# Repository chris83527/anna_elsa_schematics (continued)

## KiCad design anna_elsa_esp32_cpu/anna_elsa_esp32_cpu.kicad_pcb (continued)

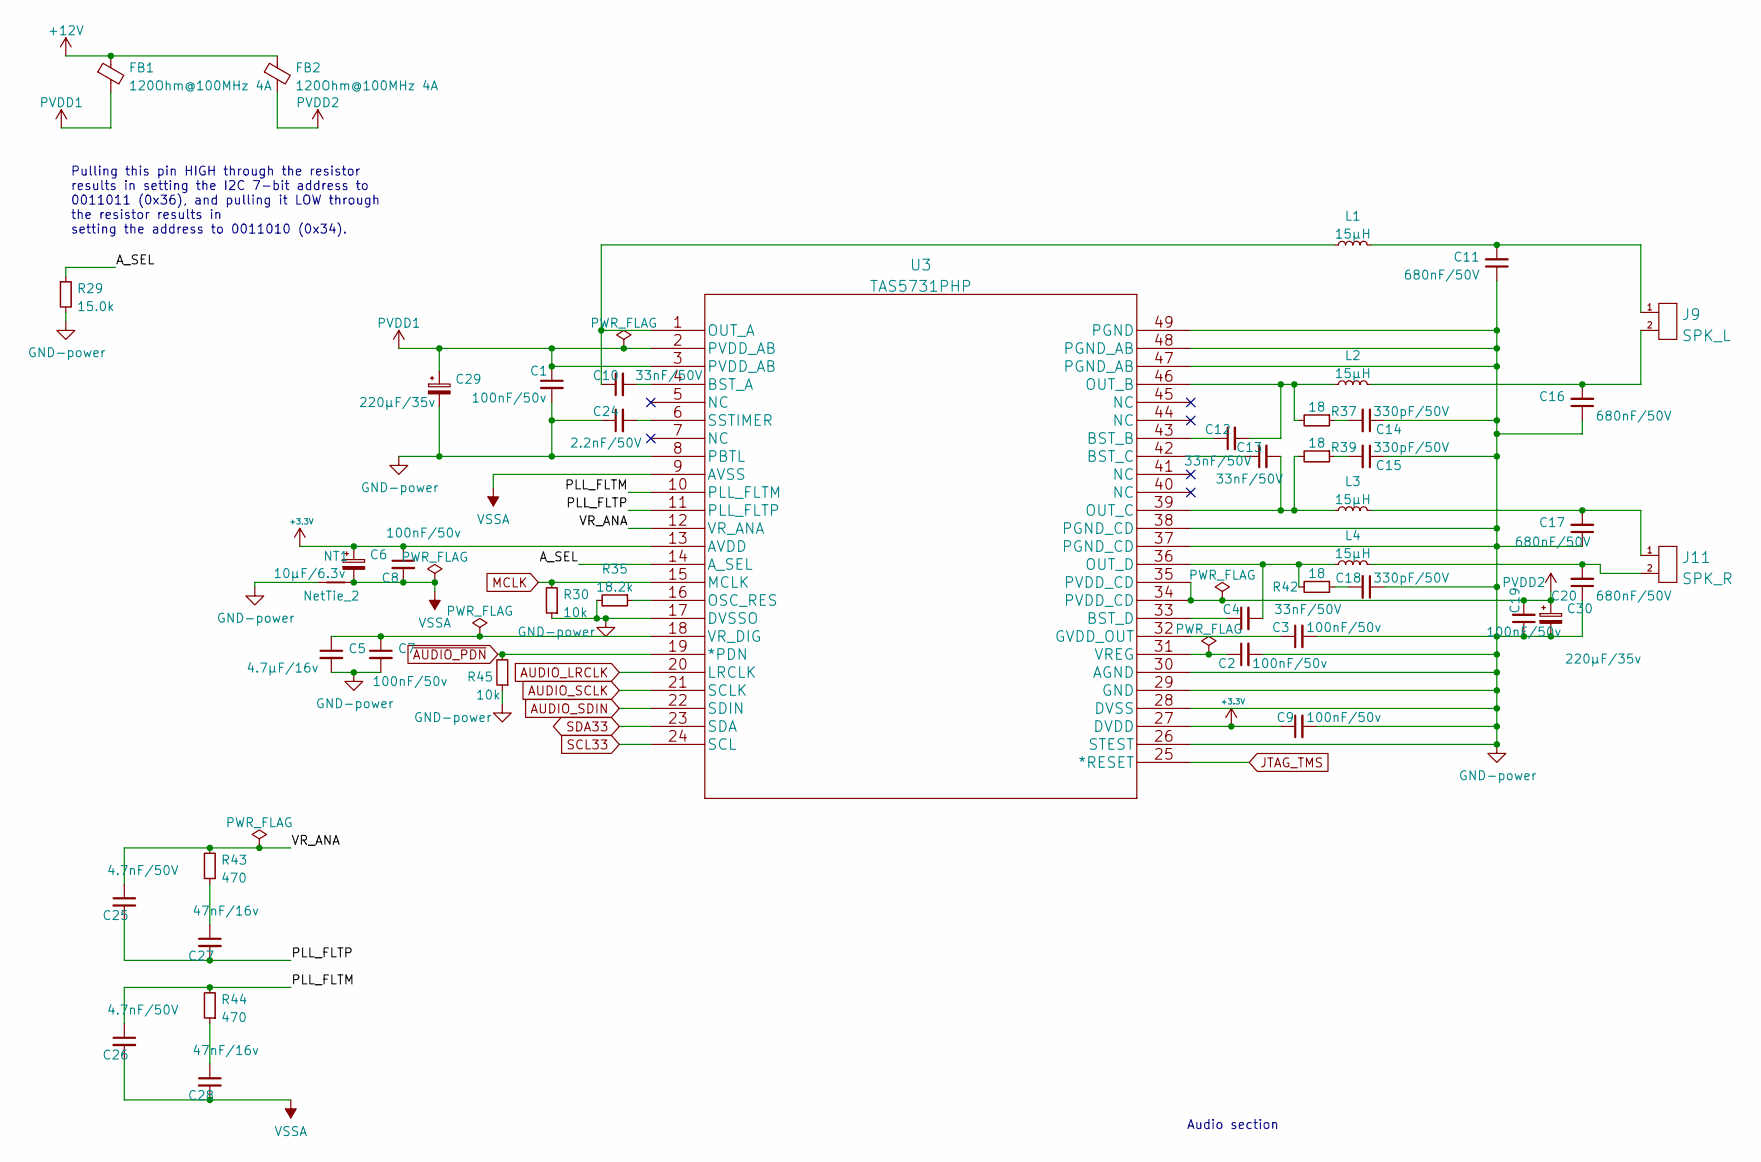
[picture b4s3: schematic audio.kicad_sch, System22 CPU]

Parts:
C1: 100nF/50v; C_0603_1608Metric; MPN CC0603KRX7R9BB104; LCSC C14663
C2, C3, C7, C8, C9, C19: 100nF/50v; C_0603_1608Metric; MPN CC0603KRX7R9BB104; JLC 0603
C4, C10, C12, C13: 33nF/50V; C_0603_1608Metric; MPN CL10B333KB8NNNC; JLC 0603
C5: 4.7µF/16v; C_0603_1608Metric; MPN CL10A475KO8NNNC; JLC 0603
C6: 10µF/6.3v; CP_Elec_4x5.4; MPN EEE1CA100SR; JLC 4x5.4mm
C11, C16, C17, C20: 680nF/50V; C_1206_3216Metric; MPN 1206B684K500CT; JLC 1206
C14, C15, C18: 330pF/50V; C_0603_1608Metric; MPN CL10C331JB8NNNC; JLC 0603
C24: 2.2nF/50V; C_0603_1608Metric; MPN CL10B221KB8NNNC; LCSC C107082
C25, C26: 4.7nF/50V; C_0603_1608Metric; MPN 0603B472K500NT; JLC 0603
C27, C28: 47nF/16v; C_0603_1608Metric; MPN CC0603KRX7R9BB473; JLC 0603
C29: 220µF/35v; C_Elec_8x10.2; MPN EEEFK1V221P; JLC C724731
C30: 220µF/35v; C_Elec_8x10.2; MPN EEEFK1V221P; LCSC C724731
FB1, FB2: 120Ohm@100MHz 4A; L_1206_3216Metric; MPN HCB3216KF-121T40; JLC 1206
J9: SPK_L; JST_XH_B2B-XH-A_1x02_P2.50mm_Vertical
J11: SPK_R; JST_XH_B2B-XH-A_1x02_P2.50mm_Vertical
L1, L2, L3, L4: 15µH; L_SigTra_SC3316F; MPN SSL0804HC-150M-N; LCSC C329909
NT1: NetTie_2; NetTie-2_SMD_Pad0.5mm
R29: 15.0k; R_0603_1608Metric; MPN 0603WAF1502T5E; JLC 0603
R30, R45: 10k; R_0603_1608Metric; MPN 0603WAF1002T5E; JLC 0603
R35: 18.2k; R_0603_1608Metric; MPN 0603WAF1822T5E; JLC 0603
R37, R39, R42: 18; R_0603_1608Metric; MPN 0603WAF180JT5E; JLC 0603
R43, R44: 470; R_0603_1608Metric; MPN 0603WAF4700T5E; JLC 0603
U3: TAS5731PHP; TQFP-48-1EP_7x7mm_P0.5mm_EP5x5mm_ThermalVias; MPN TAS5731MPHPR; JLC TQFP-48_7x7x05P

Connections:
+3.3V: C6.1, C8.1, C9.1, U3.13 (AVDD), U3.27 (DVDD); also elsewhere on the board
+12V: FB1.1, FB2.1; also elsewhere on the board
/Audio/A_SEL: R29.1, U3.14 (A_SEL)
/Audio/PLL_FLTM: C26.1, R44.2, U3.10 (PLL_FLTM)
/Audio/PLL_FLTP: C25.2, C27.2, U3.11 (PLL_FLTP)
/Audio/VR_ANA: C25.1, R43.2, U3.12 (VR_ANA)
AUDIO_LRCLK: U3.20 (LRCLK); also elsewhere on the board
AUDIO_SCLK: U3.21 (SCLK); also elsewhere on the board
AUDIO_SDIN: U3.22 (SDIN); also elsewhere on the board
JTAG_TMS: U3.25 (*RESET); also elsewhere on the board
MCLK: R30.2, U3.15 (MCLK); also elsewhere on the board
unnamed: C2.1, U3.31 (VREG)
unnamed: C3.1, U3.32 (GVDD_OUT)
unnamed: C4.1, U3.33 (BST_D)
unnamed: C4.2, L4.1, R42.2, U3.36 (OUT_D)
unnamed: C5.1, C7.1, U3.18 (VR_DIG)
unnamed: C10.1, L1.1, U3.1 (OUT_A)
unnamed: C10.2, U3.4 (BST_A)
unnamed: C11.2, J9.1, L1.2
unnamed: C12.1, U3.43 (BST_B)
unnamed: C12.2, L2.1, R37.2, U3.46 (OUT_B)
unnamed: C13.1, U3.42 (BST_C)
unnamed: C13.2, L3.1, R39.2, U3.39 (OUT_C)
unnamed: C14.2, R37.1
unnamed: C15.2, R39.1
unnamed: C16.2, J9.2, L2.2
unnamed: C17.2, J11.1, L3.2
unnamed: C18.2, R42.1
unnamed: C20.2, J11.2, L4.2
unnamed: C24.2, U3.6 (SSTIMER)
unnamed: C27.1, R43.1
unnamed: C28.1, R44.1
unnamed: R35.1, U3.16 (OSC_RES)
PVDD1: C1.1, C29.1, FB1.2, U3.2 (PVDD_AB), U3.3 (PVDD_AB)
PVDD2: C19.2, C30.1, FB2.2, U3.34 (PVDD_CD), U3.35 (PVDD_CD)
SCL33: U3.24 (SCL); also elsewhere on the board
SDA33: U3.23 (SDA); also elsewhere on the board
VSSA: C6.2, C8.2, C26.2, C28.2, NT1.2, U3.9 (AVSS)
~AUDIO_PDN: R45.2, U3.19 (*PDN); also elsewhere on the board

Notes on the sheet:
Audio section
Pulling this pin HIGH through the resistor results in setting the I2C 7-bit address to 0011011 (0x36), and pulling it LOW through the resistor results in setting the address to 0011010 (0x34).

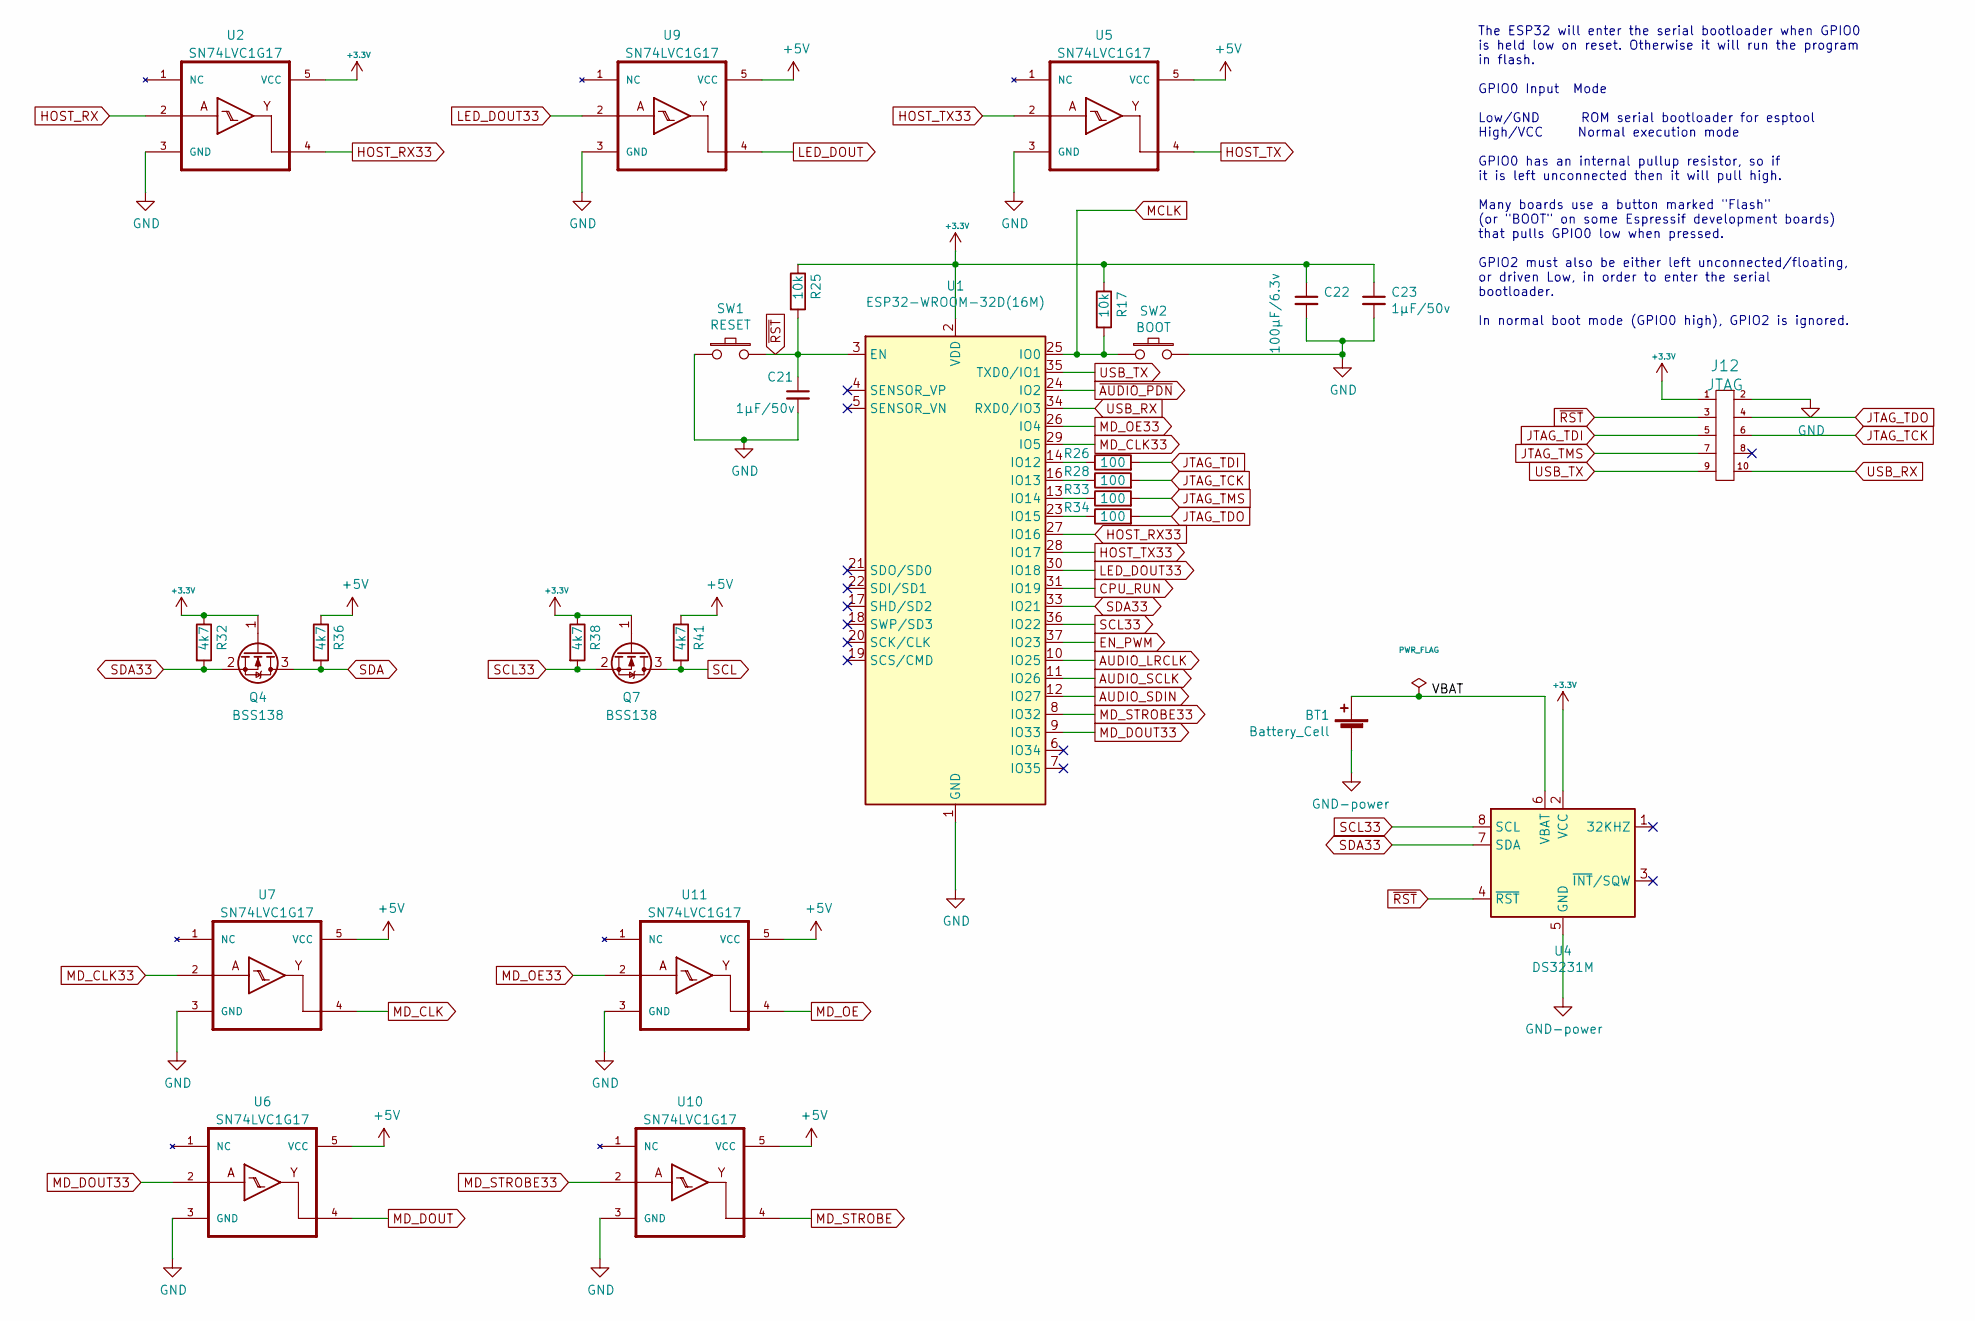
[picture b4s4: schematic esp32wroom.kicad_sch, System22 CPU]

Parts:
BT1: Battery_Cell; BatteryHolder_Keystone_1060_1x2032; JLC SMD
C21, C23: 1µF/50v; C_0805_2012Metric; MPN CL21B105KBFNNNE; LCSC C28323
C22: 100µF/6.3v; C_1206_3216Metric; MPN CL31A107MQHNNNE; LCSC C15008
J12: JTAG; IDC-Header_2x05_P2.54mm_Vertical
Q4, Q7: BSS138; SOT-23; MPN BSS138L; LCSC C890265
R17, R25: 10k; R_0603_1608Metric; MPN 0603WAF1002T5E; LCSC C25804
R26, R28, R33, R34: 100; R_0603_1608Metric; MPN 0603WAF1000T5E; LCSC C22775
R32, R36, R38, R41: 4k7; R_0603_1608Metric; MPN MCR03EZPJ472; LCSC C123022
SW1: RESET; SW_SPST_Omron_B3FS-100xP; MPN B3FS-1002P; JLC 6x3.1mm
SW2: BOOT; SW_SPST_Omron_B3FS-100xP; MPN B3FS-1002P; JLC 6x3.1mm
U1: ESP32-WROOM-32D(16M); ESP32-WROOM-32; MPN ESP32-WROOM-32D(16MB); LCSC C529578
U2: SN74LVC1G17; SOT-353_SC-70-5; MPN SN74LVC1G17DCKR; LCSC C10425
U4: DS3231M; SOIC-8_3.9x4.9mm_P1.27mm; MPN DS3231MZ+TRL; LCSC C107410
U5, U6, U10, U11: SN74LVC1G17; SOT-353_SC-70-5; LCSC C10425
U7: SN74LVC1G17; SOT-353_SC-70-5; MPN SN74LVC1G17QDBVRQ1; LCSC C10425
U9: SN74LVC1G17; SOT-353_SC-70-5; MPN SN74LVC1G17QDBVRQ; LCSC C10425

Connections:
+3.3V: C22.1, C23.1, J12.1, Q4.1 (G), Q7.1 (G), R17.1, R25.1, R32.1, R38.1, U1.2 (VDD), U2.5 (VCC), U4.2 (VCC); also elsewhere on the board
+5V: R36.1, R41.1, U5.5 (VCC), U6.5 (VCC), U7.5 (VCC), U9.5 (VCC), U10.5 (VCC), U11.5 (VCC); also elsewhere on the board
/ESP32-Wroom/VBAT: BT1.1 (+), U4.6 (VBAT)
AUDIO_LRCLK: U1.10 (IO25); also elsewhere on the board
AUDIO_SCLK: U1.11 (IO26); also elsewhere on the board
AUDIO_SDIN: U1.12 (IO27); also elsewhere on the board
CPU_RUN: U1.31 (IO19); also elsewhere on the board
EN_PWM: U1.37 (IO23); also elsewhere on the board
HOST_RX: U2.2; also elsewhere on the board
HOST_RX33: U1.27 (IO16), U2.4
HOST_TX: U5.4; also elsewhere on the board
HOST_TX33: U1.28 (IO17), U5.2
JTAG_TCK: J12.6, R28.2
JTAG_TDI: J12.5, R26.2
JTAG_TDO: J12.4, R34.2
JTAG_TMS: J12.7, R33.2; also elsewhere on the board
LED_DOUT: U9.4; also elsewhere on the board
LED_DOUT33: U1.30 (IO18), U9.2
MCLK: R17.2, SW2.1, U1.25 (IO0); also elsewhere on the board
MD_CLK: U7.4; also elsewhere on the board
MD_CLK33: U1.29 (IO5), U7.2
MD_DOUT: U6.4; also elsewhere on the board
MD_DOUT33: U1.9 (IO33), U6.2
MD_OE: U11.4; also elsewhere on the board
MD_OE33: U1.26 (IO4), U11.2
MD_STROBE: U10.4; also elsewhere on the board
MD_STROBE33: U1.8 (IO32), U10.2
unnamed: R26.1, U1.14 (IO12)
unnamed: R28.1, U1.16 (IO13)
unnamed: R33.1, U1.13 (IO14)
unnamed: R34.1, U1.23 (IO15)
SCL: Q7.3 (D), R41.2; also elsewhere on the board
SCL33: Q7.2 (S), R38.2, U1.36 (IO22), U4.8 (SCL); also elsewhere on the board
SDA: Q4.3 (D), R36.2; also elsewhere on the board
SDA33: Q4.2 (S), R32.2, U1.33 (IO21), U4.7 (SDA); also elsewhere on the board
USB_RX: J12.10, U1.34 (RXD0/IO3)
USB_TX: J12.9, U1.35 (TXD0/IO1)
~AUDIO_PDN: U1.24 (IO2); also elsewhere on the board
~RST: C21.1, J12.3, R25.2, SW1.2, U1.3 (EN), U4.4 (~RST)

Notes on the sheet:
The ESP32 will enter the serial bootloader when GPIO0 is held low on reset. Otherwise it will run the program in flash. GPIO0 Input Mode Low/GND ROM serial bootloader for esptool High/VCC Normal execution mode GPIO0 has an internal pullup resistor, so if it is left unconnected then it will pull hig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

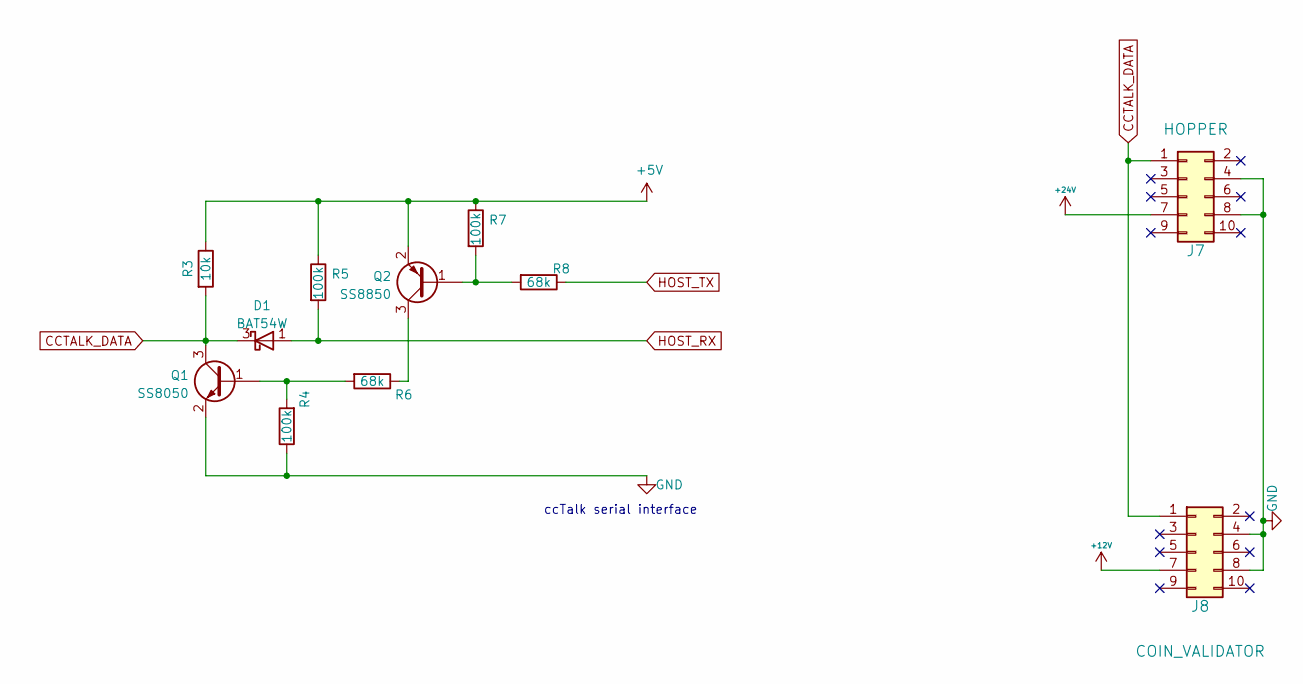
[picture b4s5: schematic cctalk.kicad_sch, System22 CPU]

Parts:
D1: BAT54W; SOT-323_SC-70
J7: HOPPER; IDC-Header_2x05_P2.54mm_Vertical
J8: COIN_VALIDATOR; IDC-Header_2x05_P2.54mm_Vertical
Q1: SS8050; SOT-23; LCSC C2150
Q2: SS8850; SOT-23; MPN SS8550 Y2; LCSC C8542
R3: 10k; R_0603_1608Metric; MPN 0603WAF1002T5E; LCSC C25804
R4, R5, R7: 100k; R_0805_2012Metric; MPN 0805W8F100KT5E; LCSC C280011
R6, R8: 68k; R_0805_2012Metric; LCSC C17801

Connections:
+5V: Q2.2 (E), R3.1, R5.1, R7.1; also elsewhere on the board
+12V: J8.7; also elsewhere on the board
+24V: J7.7; also elsewhere on the board
CCTALK_DATA: D1.3 (K), J7.1, J8.1, Q1.3 (C), R3.2
HOST_RX: D1.1 (A), R5.2; also elsewhere on the board
HOST_TX: R8.1; also elsewhere on the board
unnamed: Q1.1 (B), R4.2, R6.2
unnamed: Q2.1 (B), R7.2, R8.2
unnamed: Q2.3 (C), R6.1

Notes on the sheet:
ccTalk serial interface

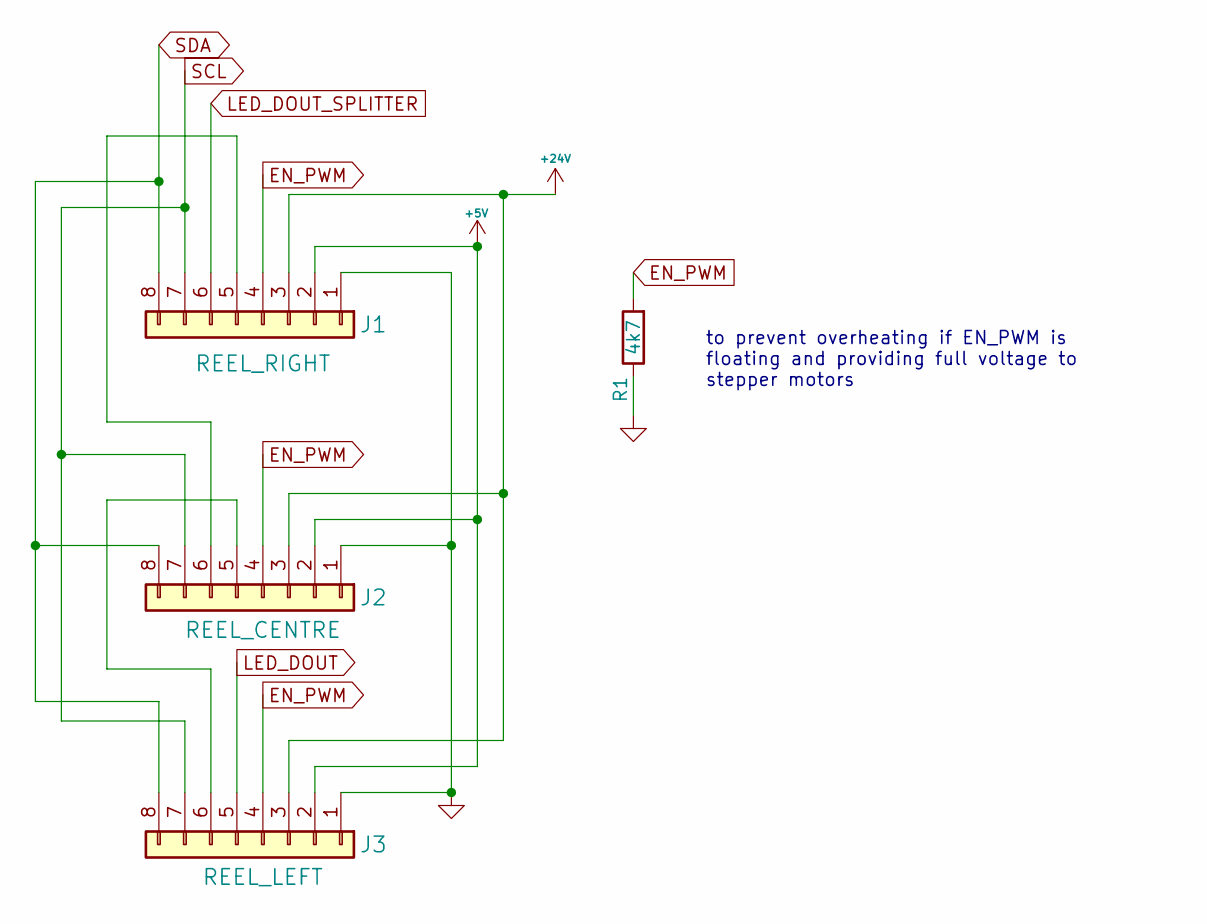
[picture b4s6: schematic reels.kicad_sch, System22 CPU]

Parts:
J1: REEL_RIGHT; JST_XH_B8B-XH-A_1x08_P2.50mm_Vertical
J2: REEL_CENTRE; JST_XH_B8B-XH-A_1x08_P2.50mm_Vertical
J3: REEL_LEFT; JST_XH_B8B-XH-A_1x08_P2.50mm_Vertical
R1: 4k7; R_0805_2012Metric; LCSC C17673

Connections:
+5V: J1.2, J2.2, J3.2; also elsewhere on the board
+24V: J1.3, J2.3, J3.3; also elsewhere on the board
EN_PWM: J1.4, J2.4, J3.4, R1.2; also elsewhere on the board
LED_DOUT: J3.5; also elsewhere on the board
LED_DOUT_SPLITTER: J1.6; also elsewhere on the board
unnamed: J1.5, J2.6
unnamed: J2.5, J3.6
SCL: J1.7, J2.7, J3.7; also elsewhere on the board
SDA: J1.8, J2.8, J3.8; also elsewhere on the board

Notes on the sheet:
to prevent overheating if EN_PWM is floating and providing full voltage to stepper motors

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
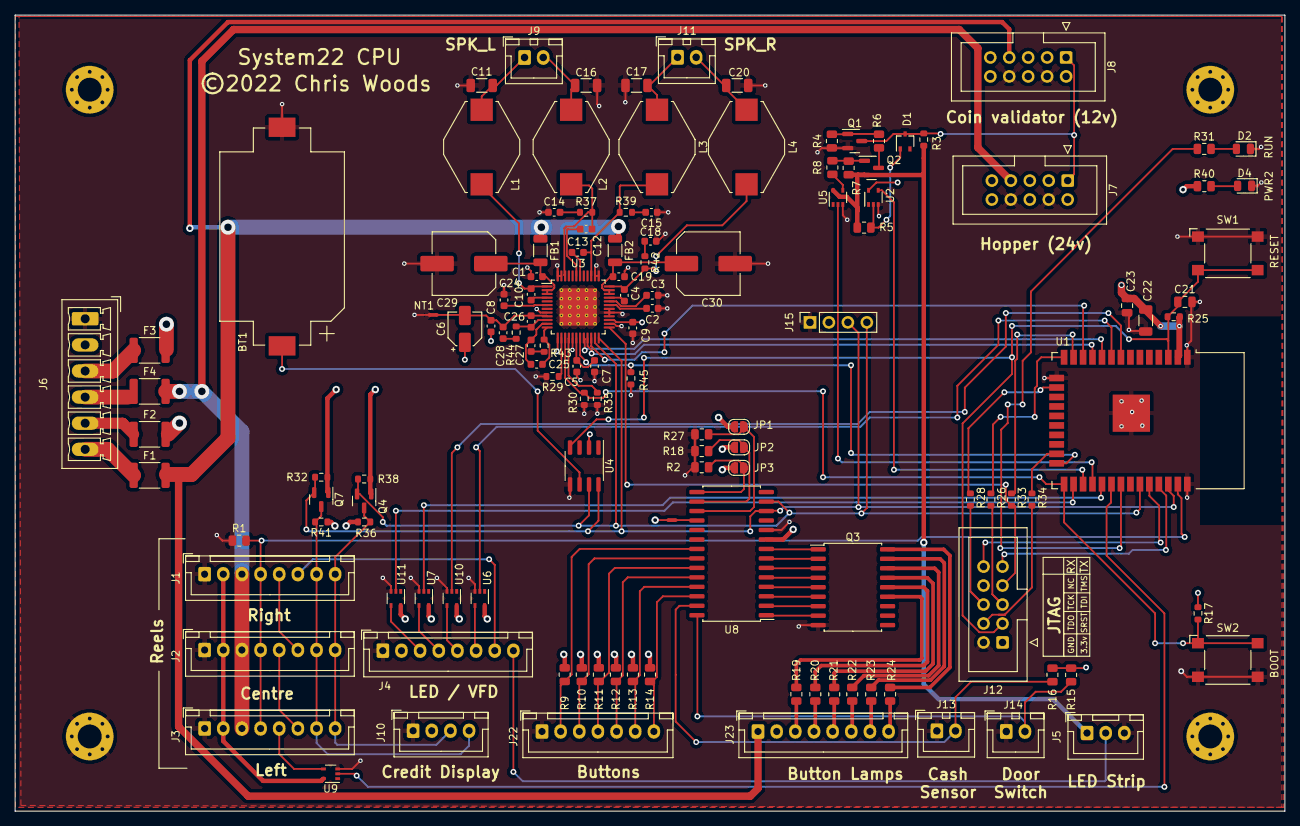
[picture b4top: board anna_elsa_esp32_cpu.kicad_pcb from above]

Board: 4 copper layers, 170.2 x 106.7 mm, 133 parts (0 on the bottom side), 117 nets.

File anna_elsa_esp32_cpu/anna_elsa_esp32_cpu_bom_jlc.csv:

"Comment","Designator","Footprint","LCSC Part #"
"Battery_Cell","BT1","BatteryHolder_Keystone_1060_1x2032","C238069"
"100nF/50v","C1,C2,C3,C7,C8,C9,C19","C_0603_1608Metric","C14663"
"33nF/50V","C4,C10,C12,C13","C_0603_1608Metric","C21117"
"4.7µF/16v","C5","C_0603_1608Metric","C19666"
"10µF/6.3v","C6","CP_Elec_4x5.4","C178496"
"680nF/50V","C11,C16,C17,C20","C_1206_3216Metric","C396794"
"330pF/50V","C14,C15,C18","C_0603_1608Metric","C1664"
"1µF/50v","C21,C23","C_0805_2012Metric","C28323"
"100µF/6.3v","C22","C_1206_3216Metric","C15008"
"220pF/50V","C24","C_0603_1608Metric","C1603"
"4.7nF/50V","C25,C26","C_0603_1608Metric","C53987"
"470nF/16v","C27,C28","C_0603_1608Metric","C194073"
"220µF/35v","C29,C30","C_Elec_8x10.2","C724731"
"RUN","D2","LED_0805_2012Metric","C84256"
"BAT54","D3","SOT-23","C37704"
"PWR2","D4","LED_0805_2012Metric","C84256"
"2A 30V","F1,F2,F3,F4","Fuse_1812_4532Metric","C960026"
"120Ohm@100MHz 4A","FB1,FB2","L_1206_3216Metric","C369528"
"15µH","L1,L2,L3,L4","L_SigTra_SC3316F","C329909"
"SS8050","Q1","SOT-23","C2150"
"SS8850","Q2","SOT-23","C8542"
"ULN2803ADWR","Q3","SOIC-18W_7.5x11.6mm_P1.27mm","C9683"
"BSS138","Q4,Q7","SOT-23","C890265"
"4k7","R2,R9,R10,R11,R12,R13,R14,R15,R16,R18,R27,R1","R_0805_2012Metric","C17673"
"100k","R4,R5,R7","R_0805_2012Metric","C25271"
"68k","R6,R8","R_0805_2012Metric","C17801"
"22","R19,R20,R21,R22,R23,R24","R_0805_2012Metric","C17561"
"100","R26,R28,R33,R34","R_0603_1608Metric","C22775"
"15.0k","R29","R_0603_1608Metric","C22809"
"10k","R30,R45,R17,R25,R32,R36,R38,R41,R3","R_0603_1608Metric","C25804"
"180","R31,R40","R_0805_2012Metric","C25270"
"18.2k","R35","R_0603_1608Metric","C22892"
"18","R37,R39,R42","R_0603_1608Metric","C22830"
"470","R43,R44","R_0603_1608Metric","C23179"
"RESET","SW1","SW_SPST_Omron_B3FS-100xP","C87038"
"BOOT","SW2","SW_SPST_Omron_B3FS-100xP","C87038"
"ESP32-WROOM-32D(16M)","U1","ESP32-WROOM-32","C529578"
"SN74LVC1G17","U2,U5,U6,U7,U9,U10,U11","SOT-353_SC-70-5","C10425"
"TAS5731PHP","U3","TQFP-48-1EP_7x7mm_P0.5mm_EP5x5mm_ThermalVias","C181751"
"DS3231M","U4","SOIC-8_3.9x4.9mm_P1.27mm","C107410"
"MCP23017T-E/SO","U8","SOIC-28W_7.5x17.9mm_P1.27mm","C629440"

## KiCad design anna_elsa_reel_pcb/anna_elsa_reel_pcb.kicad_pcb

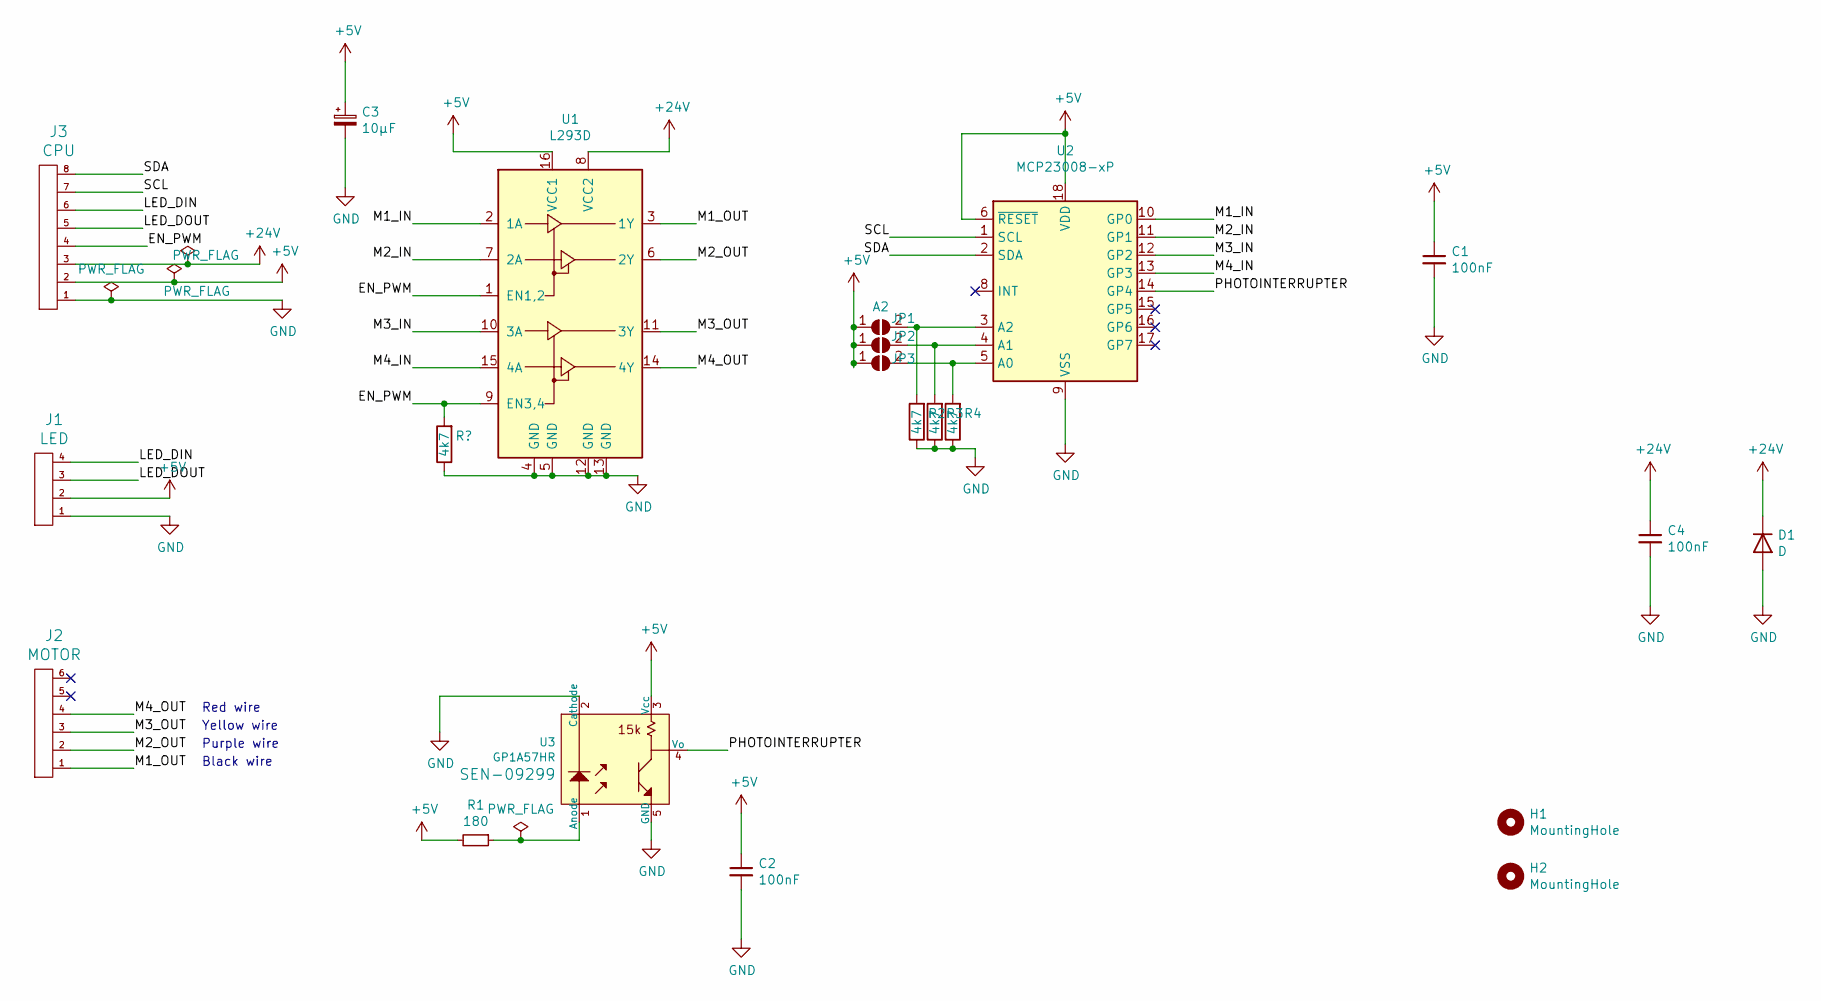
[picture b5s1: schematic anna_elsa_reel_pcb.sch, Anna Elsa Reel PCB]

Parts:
C1, C4: 100nF; C_Rect_L7.0mm_W2.0mm_P5.00mm
C2: 100nF; C_Disc_D3.0mm_W1.6mm_P2.50mm
C3: 10µF; CP_Radial_D5.0mm_P2.00mm
D1: D; D_DO-34_SOD68_P7.62mm_Horizontal
H1, H2: MountingHole; MountingHole_3mm
J1: LED; JST_XH_B4B-XH-A_1x04_P2.50mm_Vertical
J2: MOTOR; JST_XH_B6B-XH-A_1x06_P2.50mm_Vertical
J3: CPU; JST_XH_B8B-XH-A_1x08_P2.50mm_Vertical
JP1: A2; SolderJumper-2_P1.3mm_Open_RoundedPad1.0x1.5mm
JP2: A1; SolderJumper-2_P1.3mm_Open_RoundedPad1.0x1.5mm
JP3: A0; SolderJumper-2_P1.3mm_Open_RoundedPad1.0x1.5mm
R1: 180; R_Axial_DIN0207_L6.3mm_D2.5mm_P10.16mm_Horizontal
R2, R3, R4: 4k7; R_Axial_DIN0207_L6.3mm_D2.5mm_P10.16mm_Horizontal
U1: L293D; DIP-16_W7.62mm; MPN L293D; Digi-Key_PN 497-2936-5-ND
U2: MCP23008-xP; DIP-18_W7.62mm
U3: GP1A57HR

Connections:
+5V: C1.1, C2.1, C3.1, J1.2, J3.2, JP1.1 (A), JP2.1 (A), JP3.1 (A), R1.2, U1.16 (VCC1), U2.6 (~RESET), U2.18 (VDD), U3.3 (Vcc)
+24V: C4.1, D1.1 (K), J3.3, U1.8 (VCC2)
/EN_PWM: J3.4, U1.1 (EN1,2), U1.9 (EN3,4)
/LED_DIN: J1.4, J3.6
/LED_DOUT: J1.3, J3.5
/M1_IN: U1.2 (1A), U2.10 (GP0)
/M1_OUT: J2.1, U1.3 (1Y)
/M2_IN: U1.7 (2A), U2.11 (GP1)
/M2_OUT: J2.2, U1.6 (2Y)
/M3_IN: U1.10 (3A), U2.12 (GP2)
/M3_OUT: J2.3, U1.11 (3Y)
/M4_IN: U1.15 (4A), U2.13 (GP3)
/M4_OUT: J2.4, U1.14 (4Y)
/PHOTOINTERRUPTER: U2.14 (GP4), U3.4 (Vo)
/SCL: J3.7, U2.1 (SCL)
/SDA: J3.8, U2.2 (SDA)
GND: C1.2, C2.2, C3.2, C4.2, D1.2 (A), J1.1, J3.1, R2.1, R3.1, R4.1, U1.4 (GND), U1.5 (GND), U1.12 (GND), U1.13 (GND), U2.9 (VSS), U3.2 (Cathode), U3.5 (GND)
unnamed: JP1.2 (B), R2.2, U2.3 (A2)
unnamed: JP2.2 (B), R3.2, U2.4 (A1)
unnamed: JP3.2 (B), R4.2, U2.5 (A0)
unnamed: R1.1, U3.1 (Anode)

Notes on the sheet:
Red wire
Yellow wire
Purple wire
Black wire

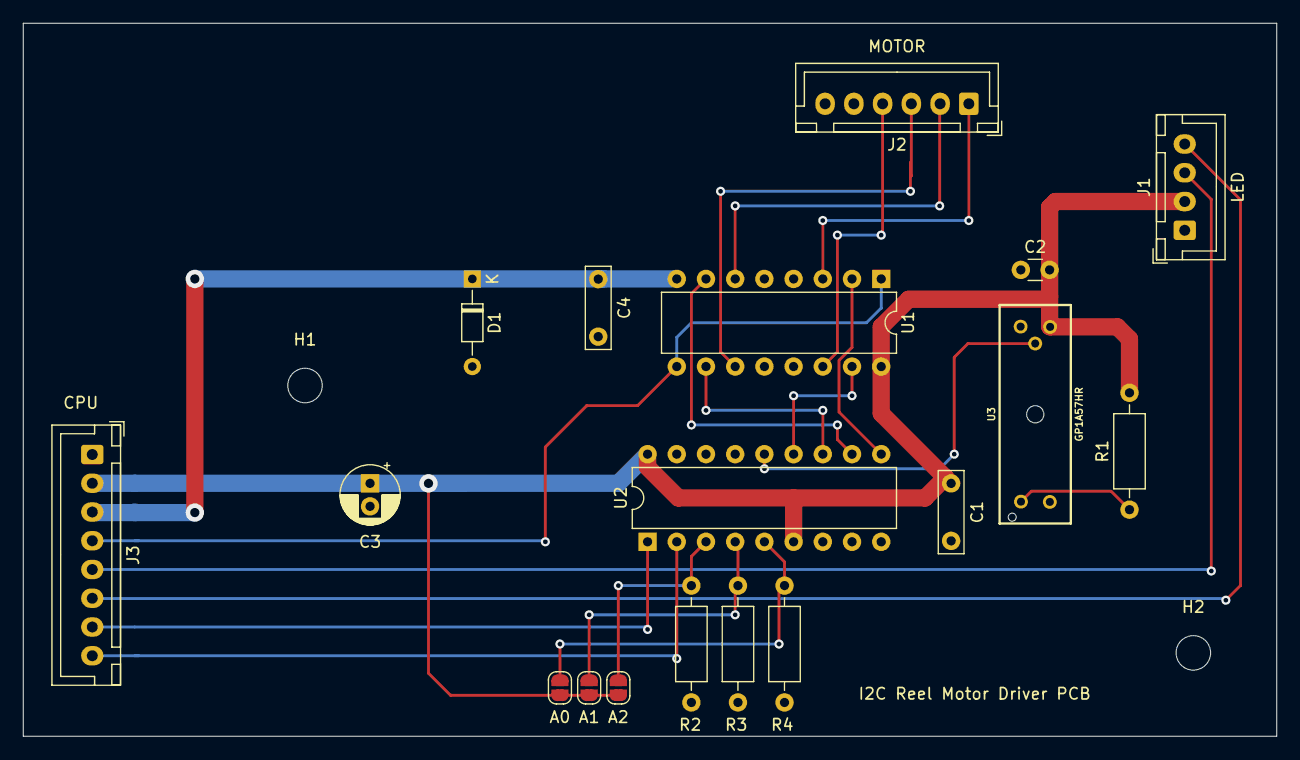
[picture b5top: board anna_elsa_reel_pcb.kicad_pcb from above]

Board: 2 copper layers, 109.0 x 62.0 mm, 20 parts (0 on the bottom side), 21 nets.

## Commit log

2022-08-02 removed redundant subdirectory
2022-08-02 Added additional schematics
2022-08-02 Removed gerbers from reel pcb directory
2022-08-02 Renamed plots directory to gerbers for consistency
2022-08-02 Removed obsolete schematics
2023-01-22 Added current cpu pcb and removed old
2023-01-22 Remvoed backup folders
2023-09-29 Latest schematics
